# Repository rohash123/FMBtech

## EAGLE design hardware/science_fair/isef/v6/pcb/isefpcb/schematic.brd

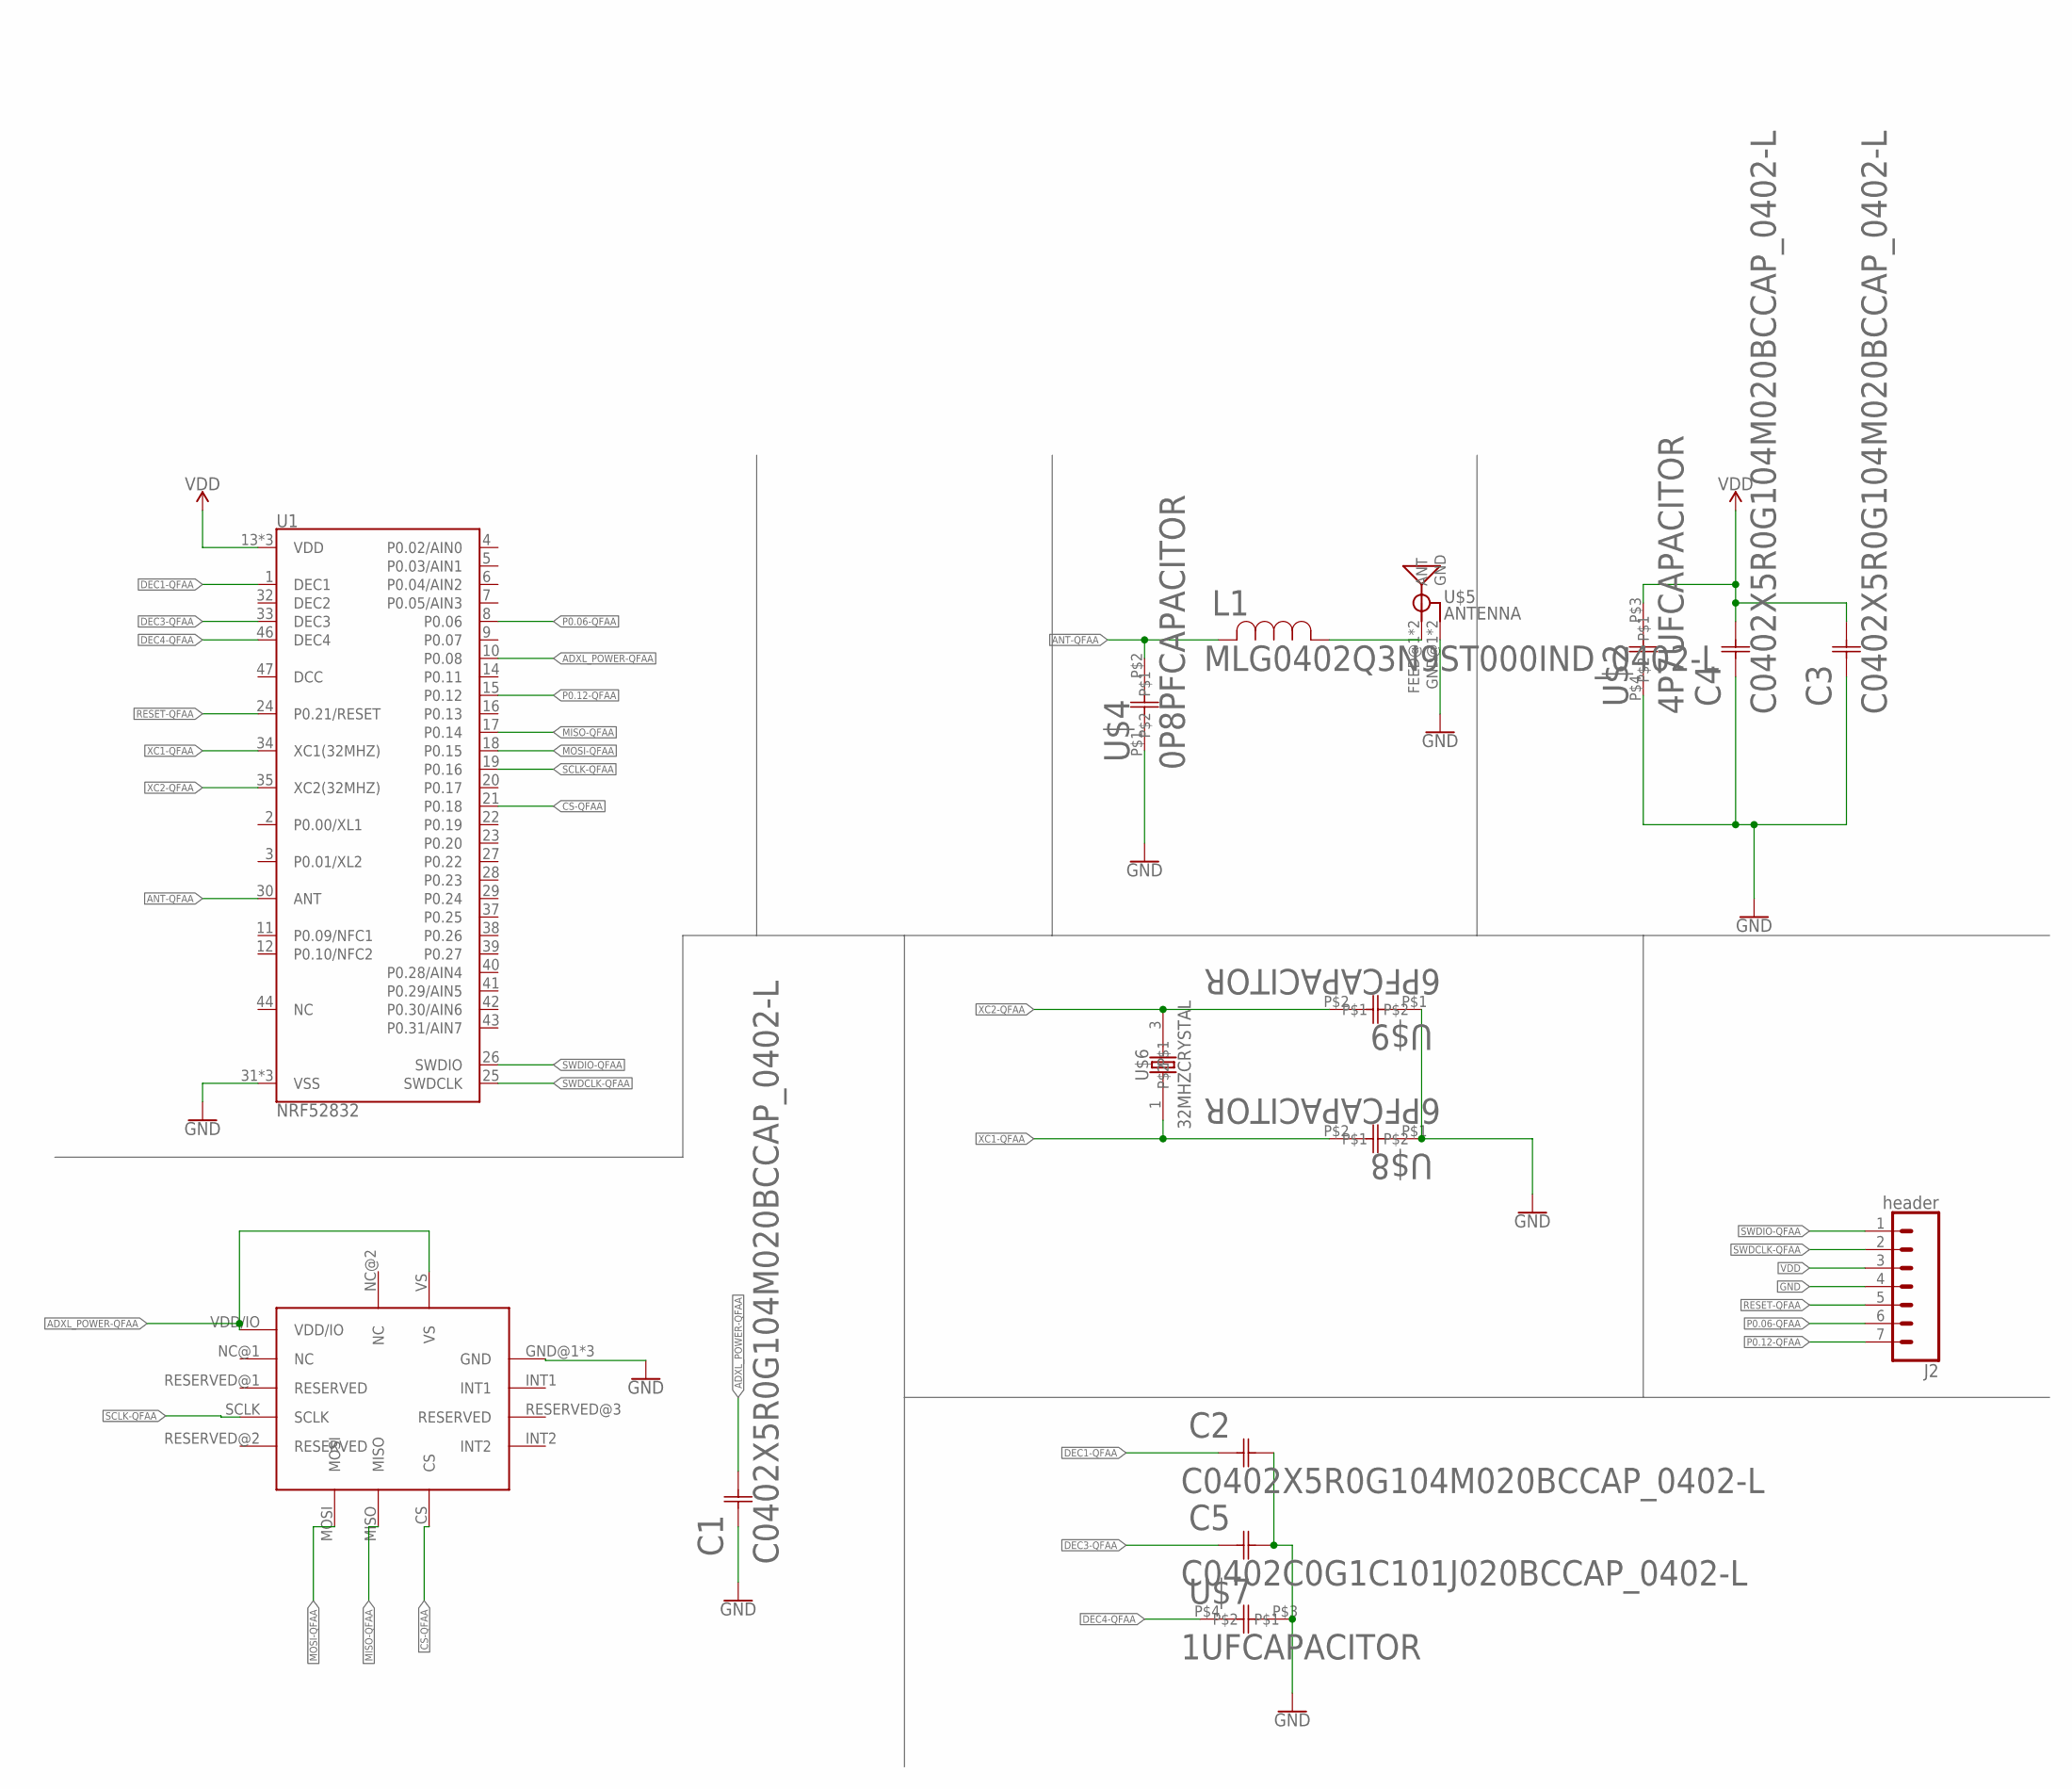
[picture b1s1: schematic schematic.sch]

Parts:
C1, C2, C3, C4: C0402X5R0G104M020BCCAP_0402-L; CAP_0402-L
C5: C0402C0G1C101J020BCCAP_0402-L; CAP_0402-L
J2: header; 1X07
L1: MLG0402Q3N9ST000IND_0402-L; IND_0402-L
U1: NRF52832; QFN48-6X6MM
U$1: ADXL362; TFLGA-16/3.3MMX3.1MM
U$2: 4P7UFCAPACITOR
U$4: 0P8PFCAPACITOR
U$5: ANTENNA; ANTENNA_FOOTPRINT
U$6: 32MHZCRYSTAL
U$7: 1UFCAPACITOR
U$8, U$9: 6PFCAPACITOR

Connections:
ADXL_POWER-QFAA: C1.2 (22), U1.10 (P0.08), U$1.VDD/IO, U$1.VS
ANT-QFAA: L1.2, U1.30 (ANT), U$4.P$2
CS-QFAA: U1.21 (P0.18), U$1.CS
DEC1-QFAA: C2.1 (11), U1.1 (DEC1)
DEC3-QFAA: C5.1 (11), U1.33 (DEC3)
DEC4-QFAA: U1.46 (DEC4), U$7.P$4
GND: C1.1 (11), C2.2 (22), C3.1 (11), C4.1 (11), C5.2 (22), J2.4, U1.31 (VSS), U1.45 (VSS), U1.EP (VSS), U$1.GND@1 (GND), U$1.GND@2 (GND), U$1.GND@3 (GND), U$2.P$4, U$4.P$1, U$5.GND@1 (GND), U$5.GND@2 (GND), U$7.P$3, U$8.P$1, U$9.P$1
MISO-QFAA: U1.17 (P0.14), U$1.MISO
MOSI-QFAA: U1.18 (P0.15), U$1.MOSI
unnamed: L1.1, U$5.FEED@1 (ANT), U$5.FEED@2 (ANT)
P0.06-QFAA: J2.6, U1.8 (P0.06)
P0.12-QFAA: J2.7, U1.15 (P0.12)
RESET-QFAA: J2.5, U1.24 (P0.21/RESET)
SCLK-QFAA: U1.19 (P0.16), U$1.SCLK
SWDCLK-QFAA: J2.2, U1.25 (SWDCLK)
SWDIO-QFAA: J2.1, U1.26 (SWDIO)
VDD: C3.2 (22), C4.2 (22), J2.3, U1.13 (VDD), U1.36 (VDD), U1.48 (VDD), U$2.P$3
XC1-QFAA: U1.34 (XC1(32MHZ)), U$6.1, U$8.P$2
XC2-QFAA: U1.35 (XC2(32MHZ)), U$6.3, U$9.P$2

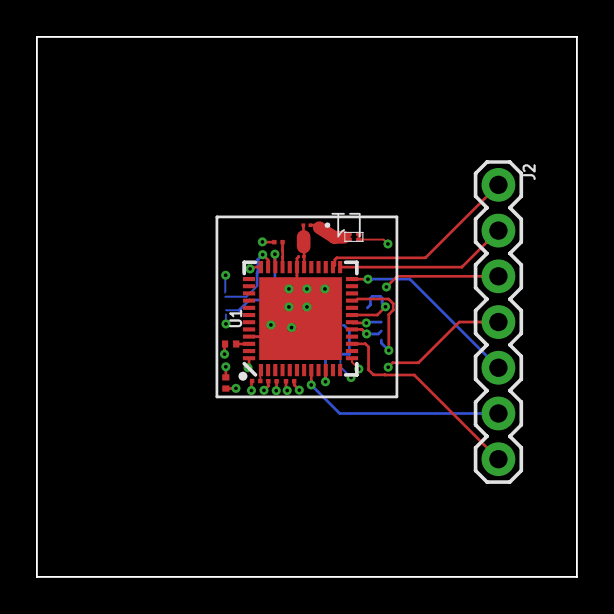
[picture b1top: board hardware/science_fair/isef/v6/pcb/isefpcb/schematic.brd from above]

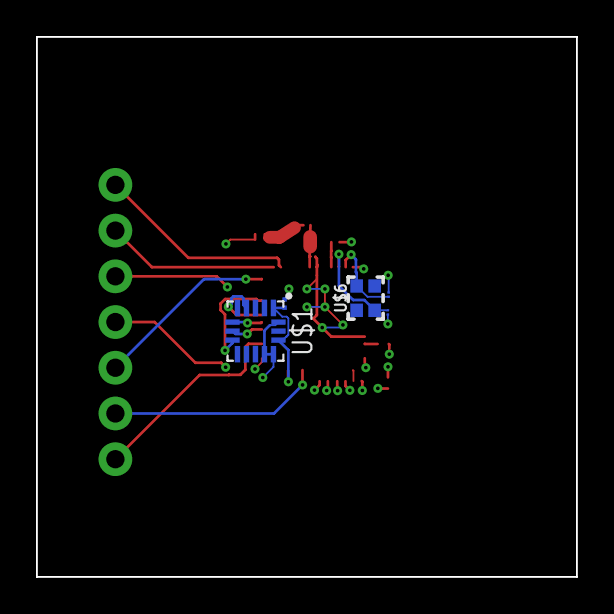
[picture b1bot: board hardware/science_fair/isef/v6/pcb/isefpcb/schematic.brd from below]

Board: 6 copper layers, 30.0 x 30.0 mm, 16 parts (5 on the bottom side), 19 nets.

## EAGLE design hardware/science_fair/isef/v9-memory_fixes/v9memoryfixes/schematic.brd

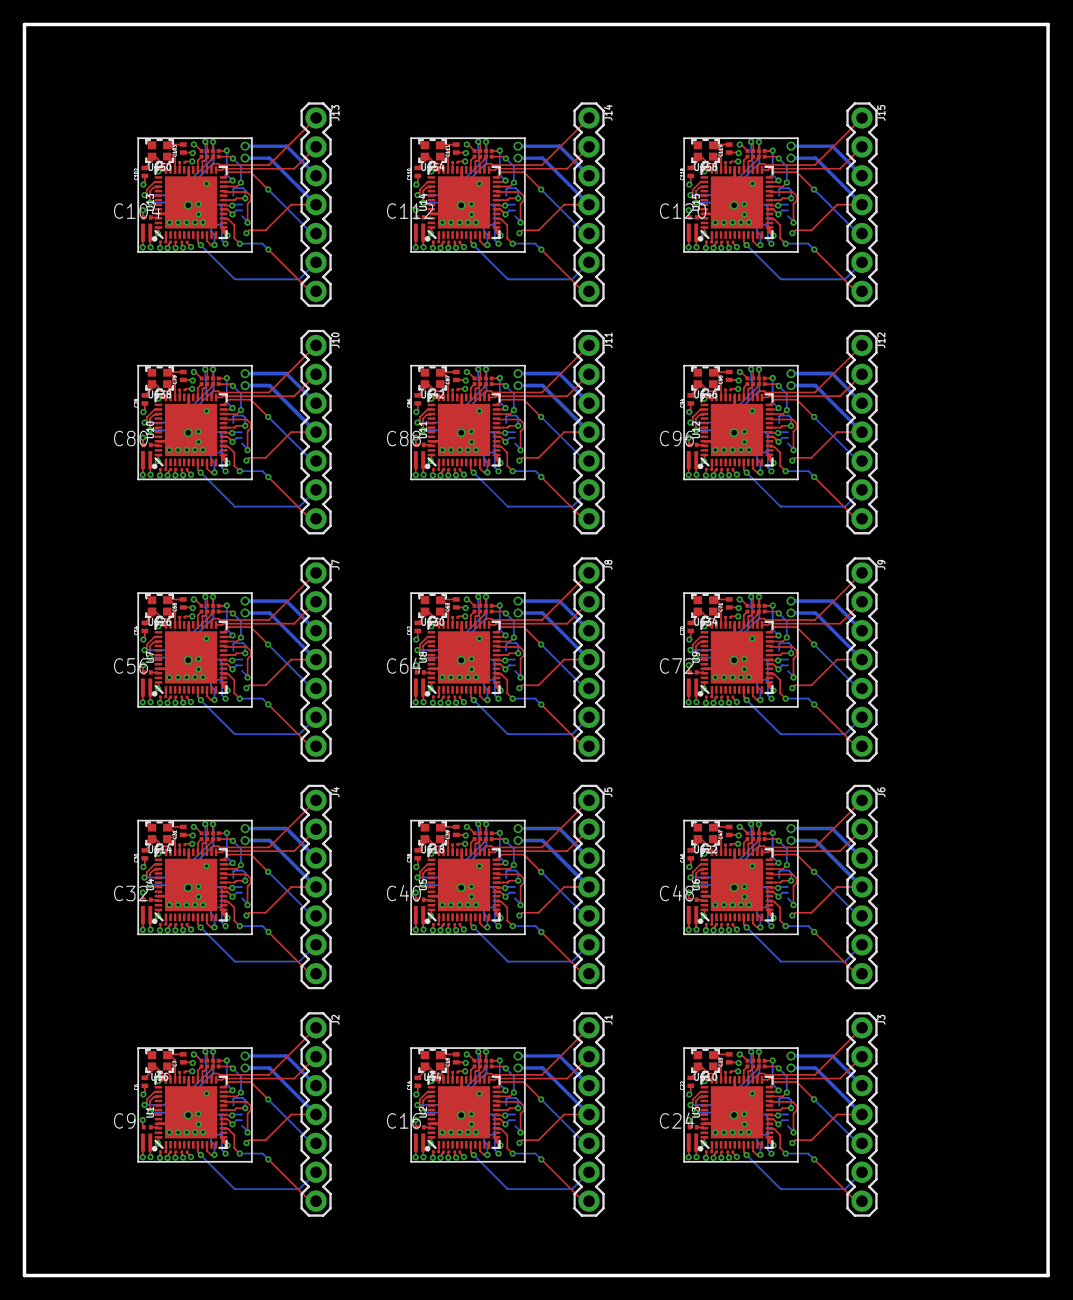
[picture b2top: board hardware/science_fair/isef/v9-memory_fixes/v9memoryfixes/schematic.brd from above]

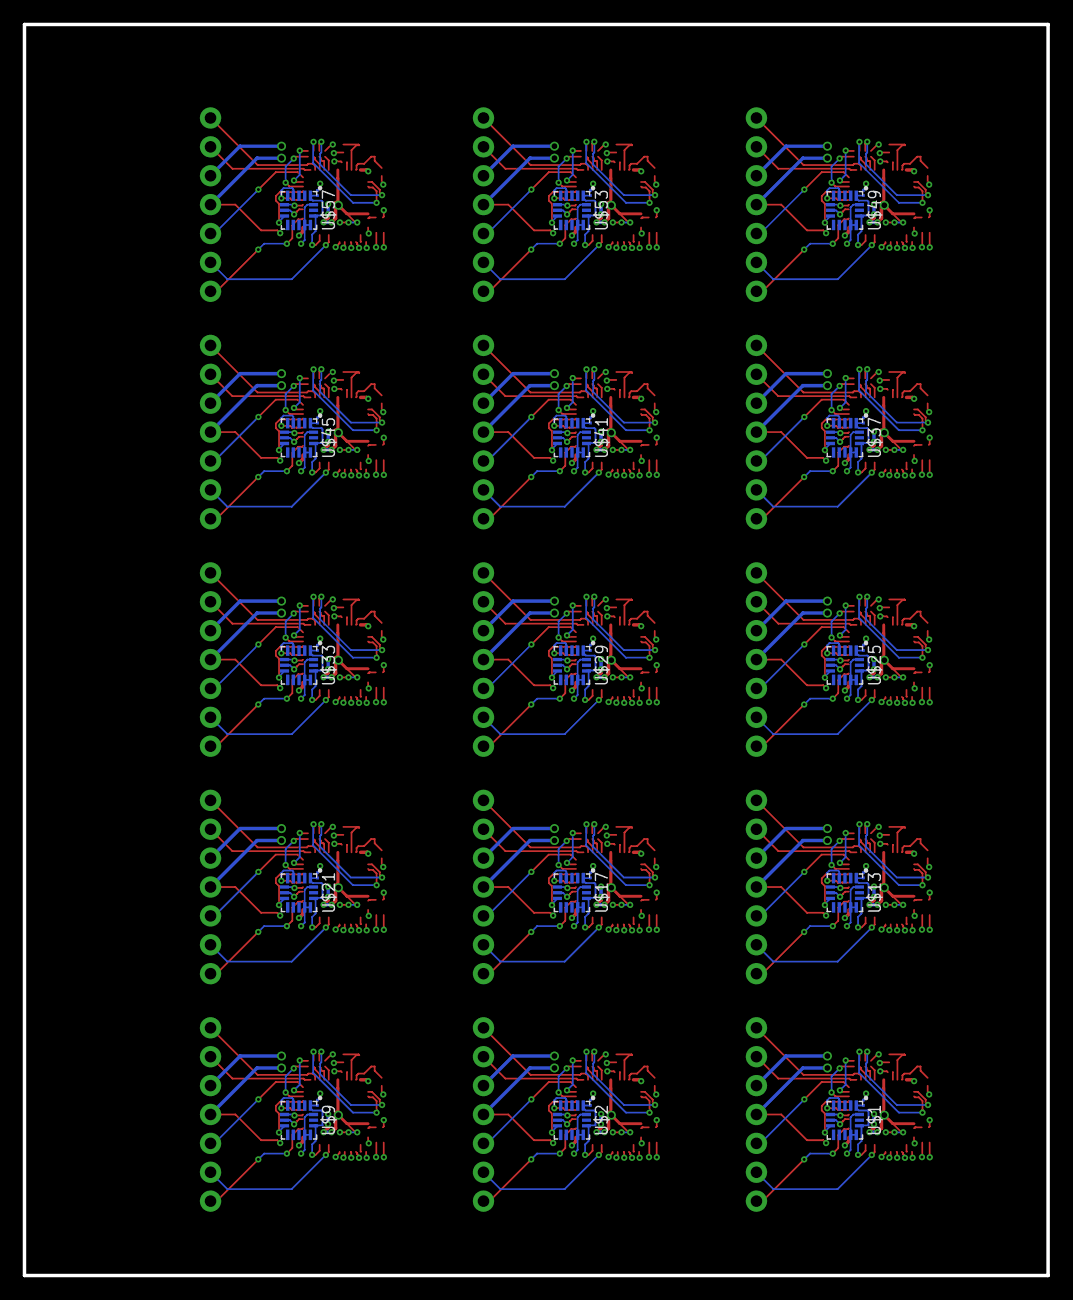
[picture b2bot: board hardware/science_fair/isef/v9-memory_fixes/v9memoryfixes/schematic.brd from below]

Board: 4 copper layers, 90.0 x 110.0 mm, 210 parts (30 on the bottom side), 360 nets.

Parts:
C1, C2, C3, C4, C8, C10, C11, C12, C17, C18, C19, C20, C25, C26, C27, C28, C33, C34, C35, C36, C41, C42, C43, C44, C49, C50, C51, C52, C57, C58, C59, C60, C65, C66, C67, C68, C73, C74, C75, C76, C81, C82, C83, C84, C89, C90, C91, C92, C97, C98, C99, C100, C105, C106, C107, C108, C113, C114, C115, C116: C0402X5R0G104M020BCCAP_0402-L; CAP_0402-L
C5, C13, C21, C29, C37, C45, C53, C61, C69, C77, C85, C93, C101, C109, C117: C0402C0G1C101J020BCCAP_0402-L; CAP_0402-L
C6, C7, C14, C15, C22, C23, C30, C31, C38, C39, C46, C47, C54, C55, C62, C63, C70, C71, C78, C79, C86, C87, C94, C95, C102, C103, C110, C111, C118, C119: GRM1555C1H6R0CA01D; CAPC1005X55N
C9, C16, C24, C32, C40, C48, C56, C64, C72, C80, C88, C96, C104, C112, C120: 4P7UFCAPACITOR4P7UFCAPACITOR; 4P7UFCAPACITOR
J1, J2, J3, J4, J5, J6, J7, J8, J9, J10, J11, J12, J13, J14, J15: header; 1X07
U1, U2, U3, U4, U5, U6, U7, U8, U9, U10, U11, U12, U13, U14, U15: NRF52832; QFN48-6X6MM
U$1, U$2, U$9, U$13, U$17, U$21, U$25, U$29, U$33, U$37, U$41, U$45, U$49, U$53, U$57: ADXL362; TFLGA-16/3.3MMX3.1MM
U$3, U$8, U$12, U$16, U$20, U$24, U$28, U$32, U$36, U$40, U$44, U$48, U$52, U$56, U$60: AT25SF161-UUD-T
U$4, U$6, U$10, U$14, U$18, U$22, U$26, U$30, U$34, U$38, U$42, U$46, U$50, U$54, U$58: 32MHZCRYSTAL
U$5, U$7, U$11, U$15, U$19, U$23, U$27, U$31, U$35, U$39, U$43, U$47, U$51, U$55, U$59: 1UFCAPACITOR

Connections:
ADXL_POWER-QFAA: C1.2, U1.10, U$1.VDD/IO, U$1.VS
ADXL_POWER-QFAA1: C8.2, U2.10, U$2.VDD/IO, U$2.VS
ADXL_POWER-QFAA2: C17.2, U3.10, U$9.VDD/IO, U$9.VS
ADXL_POWER-QFAA3: C25.2, U4.10, U$13.VDD/IO, U$13.VS
ADXL_POWER-QFAA4: C33.2, U5.10, U$17.VDD/IO, U$17.VS
ADXL_POWER-QFAA5: C41.2, U6.10, U$21.VDD/IO, U$21.VS
ADXL_POWER-QFAA6: C49.2, U7.10, U$25.VDD/IO, U$25.VS
ADXL_POWER-QFAA7: C57.2, U8.10, U$29.VDD/IO, U$29.VS
ADXL_POWER-QFAA8: C65.2, U9.10, U$33.VDD/IO, U$33.VS
ADXL_POWER-QFAA9: C73.2, U10.10, U$37.VDD/IO, U$37.VS
ADXL_POWER-QFAA10: C81.2, U11.10, U$41.VDD/IO, U$41.VS
ADXL_POWER-QFAA11: C89.2, U12.10, U$45.VDD/IO, U$45.VS
ADXL_POWER-QFAA12: C97.2, U13.10, U$49.VDD/IO, U$49.VS
ADXL_POWER-QFAA13: C105.2, U14.10, U$53.VDD/IO, U$53.VS
ADXL_POWER-QFAA14: C113.2, U15.10, U$57.VDD/IO, U$57.VS
CS-QFAA: U1.21, U$1.CS
CS-QFAA1: U2.21, U$2.CS
CS-QFAA2: U3.21, U$9.CS
CS-QFAA3: U4.21, U$13.CS
CS-QFAA4: U5.21, U$17.CS
CS-QFAA5: U6.21, U$21.CS
CS-QFAA6: U7.21, U$25.CS
CS-QFAA7: U8.21, U$29.CS
CS-QFAA8: U9.21, U$33.CS
CS-QFAA9: U10.21, U$37.CS
CS-QFAA10: U11.21, U$41.CS
CS-QFAA11: U12.21, U$45.CS
CS-QFAA12: U13.21, U$49.CS
CS-QFAA13: U14.21, U$53.CS
CS-QFAA14: U15.21, U$57.CS
CS_FLASH: U1.23, U$3.5
CS_FLASH1: U2.23, U$8.5
CS_FLASH2: U3.23, U$12.5
CS_FLASH3: U4.23, U$16.5
CS_FLASH4: U5.23, U$20.5
CS_FLASH5: U6.23, U$24.5
CS_FLASH6: U7.23, U$28.5
CS_FLASH7: U8.23, U$32.5
CS_FLASH8: U9.23, U$36.5
CS_FLASH9: U10.23, U$40.5
CS_FLASH10: U11.23, U$44.5
CS_FLASH11: U12.23, U$48.5
CS_FLASH12: U13.23, U$52.5
CS_FLASH13: U14.23, U$56.5
CS_FLASH14: U15.23, U$60.5
DEC1-QFAA: C2.1, U1.1
DEC1-QFAA1: C10.1, U2.1
DEC1-QFAA2: C18.1, U3.1
DEC1-QFAA3: C26.1, U4.1
DEC1-QFAA4: C34.1, U5.1
DEC1-QFAA5: C42.1, U6.1
DEC1-QFAA6: C50.1, U7.1
DEC1-QFAA7: C58.1, U8.1
DEC1-QFAA8: C66.1, U9.1
DEC1-QFAA9: C74.1, U10.1
DEC1-QFAA10: C82.1, U11.1
DEC1-QFAA11: C90.1, U12.1
DEC1-QFAA12: C98.1, U13.1
DEC1-QFAA13: C106.1, U14.1
DEC1-QFAA14: C114.1, U15.1
DEC3-QFAA: C5.1, U1.33
DEC3-QFAA1: C13.1, U2.33
DEC3-QFAA2: C21.1, U3.33
DEC3-QFAA3: C29.1, U4.33
DEC3-QFAA4: C37.1, U5.33
DEC3-QFAA5: C45.1, U6.33
DEC3-QFAA6: C53.1, U7.33
DEC3-QFAA7: C61.1, U8.33
DEC3-QFAA8: C69.1, U9.33
DEC3-QFAA9: C77.1, U10.33
DEC3-QFAA10: C85.1, U11.33
DEC3-QFAA11: C93.1, U12.33
DEC3-QFAA12: C101.1, U13.33
DEC3-QFAA13: C109.1, U14.33
DEC3-QFAA14: C117.1, U15.33
DEC4-QFAA: U1.46, U$7.P$4
DEC4-QFAA1: U2.46, U$5.P$4
DEC4-QFAA2: U3.46, U$11.P$4
DEC4-QFAA3: U4.46, U$15.P$4
DEC4-QFAA4: U5.46, U$19.P$4
DEC4-QFAA5: U6.46, U$23.P$4
DEC4-QFAA6: U7.46, U$27.P$4
DEC4-QFAA7: U8.46, U$31.P$4
DEC4-QFAA8: U9.46, U$35.P$4
DEC4-QFAA9: U10.46, U$39.P$4
DEC4-QFAA10: U11.46, U$43.P$4
DEC4-QFAA11: U12.46, U$47.P$4
DEC4-QFAA12: U13.46, U$51.P$4
DEC4-QFAA13: U14.46, U$55.P$4
DEC4-QFAA14: U15.46, U$59.P$4
FLASH_POWER: U1.22, U$3.1
FLASH_POWER1: U2.22, U$8.1
FLASH_POWER2: U3.22, U$12.1
FLASH_POWER3: U4.22, U$16.1
FLASH_POWER4: U5.22, U$20.1
FLASH_POWER5: U6.22, U$24.1
FLASH_POWER6: U7.22, U$28.1
FLASH_POWER7: U8.22, U$32.1
FLASH_POWER8: U9.22, U$36.1
FLASH_POWER9: U10.22, U$40.1
FLASH_POWER10: U11.22, U$44.1
FLASH_POWER11: U12.22, U$48.1
FLASH_POWER12: U13.22, U$52.1
FLASH_POWER13: U14.22, U$56.1
FLASH_POWER14: U15.22, U$60.1
GND: C1.1, C2.2, C3.1, C4.1, C5.2, C6.1, C7.1, C9.1, J2.4, U1.31, U1.45, U1.EP, U$1.GND@1, U$1.GND@2, U$1.GND@3, U$3.8, U$7.P$3
GND1: C8.1, C10.2, C11.1, C12.1, C13.2, C14.1, C15.1, C16.1, J1.4, U2.31, U2.45, U2.EP, U$2.GND@1, U$2.GND@2, U$2.GND@3, U$5.P$3, U$8.8
GND2: C17.1, C18.2, C19.1, C20.1, C21.2, C22.1, C23.1, C24.1, J3.4, U3.31, U3.45, U3.EP, U$9.GND@1, U$9.GND@2, U$9.GND@3, U$11.P$3, U$12.8
GND3: C25.1, C26.2, C27.1, C28.1, C29.2, C30.1, C31.1, C32.1, J4.4, U4.31, U4.45, U4.EP, U$13.GND@1, U$13.GND@2, U$13.GND@3, U$15.P$3, U$16.8
GND4: C33.1, C34.2, C35.1, C36.1, C37.2, C38.1, C39.1, C40.1, J5.4, U5.31, U5.45, U5.EP, U$17.GND@1, U$17.GND@2, U$17.GND@3, U$19.P$3, U$20.8
GND5: C41.1, C42.2, C43.1, C44.1, C45.2, C46.1, C47.1, C48.1, J6.4, U6.31, U6.45, U6.EP, U$21.GND@1, U$21.GND@2, U$21.GND@3, U$23.P$3, U$24.8
GND6: C49.1, C50.2, C51.1, C52.1, C53.2, C54.1, C55.1, C56.1, J7.4, U7.31, U7.45, U7.EP, U$25.GND@1, U$25.GND@2, U$25.GND@3, U$27.P$3, U$28.8
GND7: C57.1, C58.2, C59.1, C60.1, C61.2, C62.1, C63.1, C64.1, J8.4, U8.31, U8.45, U8.EP, U$29.GND@1, U$29.GND@2, U$29.GND@3, U$31.P$3, U$32.8
GND8: C65.1, C66.2, C67.1, C68.1, C69.2, C70.1, C71.1, C72.1, J9.4, U9.31, U9.45, U9.EP, U$33.GND@1, U$33.GND@2, U$33.GND@3, U$35.P$3, U$36.8
GND9: C73.1, C74.2, C75.1, C76.1, C77.2, C78.1, C79.1, C80.1, J10.4, U10.31, U10.45, U10.EP, U$37.GND@1, U$37.GND@2, U$37.GND@3, U$39.P$3, U$40.8
GND10: C81.1, C82.2, C83.1, C84.1, C85.2, C86.1, C87.1, C88.1, J11.4, U11.31, U11.45, U11.EP, U$41.GND@1, U$41.GND@2, U$41.GND@3, U$43.P$3, U$44.8
GND11: C89.1, C90.2, C91.1, C92.1, C93.2, C94.1, C95.1, C96.1, J12.4, U12.31, U12.45, U12.EP, U$45.GND@1, U$45.GND@2, U$45.GND@3, U$47.P$3, U$48.8
GND12: C97.1, C98.2, C99.1, C100.1, C101.2, C102.1, C103.1, C104.1, J13.4, U13.31, U13.45, U13.EP, U$49.GND@1, U$49.GND@2, U$49.GND@3, U$51.P$3, U$52.8
GND13: C105.1, C106.2, C107.1, C108.1, C109.2, C110.1, C111.1, C112.1, J14.4, U14.31, U14.45, U14.EP, U$53.GND@1, U$53.GND@2, U$53.GND@3, U$55.P$3, U$56.8
GND14: C113.1, C114.2, C115.1, C116.1, C117.2, C118.1, C119.1, C120.1, J15.4, U15.31, U15.45, U15.EP, U$57.GND@1, U$57.GND@2, U$57.GND@3, U$59.P$3, U$60.8
HOLD_FLASH: U1.27, U$3.2
HOLD_FLASH1: U2.27, U$8.2
HOLD_FLASH2: U3.27, U$12.2
HOLD_FLASH3: U4.27, U$16.2
HOLD_FLASH4: U5.27, U$20.2
HOLD_FLASH5: U6.27, U$24.2
HOLD_FLASH6: U7.27, U$28.2
HOLD_FLASH7: U8.27, U$32.2
HOLD_FLASH8: U9.27, U$36.2
HOLD_FLASH9: U10.27, U$40.2
HOLD_FLASH10: U11.27, U$44.2
HOLD_FLASH11: U12.27, U$48.2
HOLD_FLASH12: U13.27, U$52.2
HOLD_FLASH13: U14.27, U$56.2
HOLD_FLASH14: U15.27, U$60.2
MISO-QFAA: U1.17, U$1.MISO
MISO-QFAA1: U2.17, U$2.MISO
MISO-QFAA2: U3.17, U$9.MISO
MISO-QFAA3: U4.17, U$13.MISO
MISO-QFAA4: U5.17, U$17.MISO
MISO-QFAA5: U6.17, U$21.MISO
MISO-QFAA6: U7.17, U$25.MISO
MISO-QFAA7: U8.17, U$29.MISO
MISO-QFAA8: U9.17, U$33.MISO
MISO-QFAA9: U10.17, U$37.MISO
MISO-QFAA10: U11.17, U$41.MISO
MISO-QFAA11: U12.17, U$45.MISO
MISO-QFAA12: U13.17, U$49.MISO
MISO-QFAA13: U14.17, U$53.MISO
MISO-QFAA14: U15.17, U$57.MISO
MOSI-QFAA: U1.18, U$1.MOSI
MOSI-QFAA1: U2.18, U$2.MOSI
MOSI-QFAA2: U3.18, U$9.MOSI
MOSI-QFAA3: U4.18, U$13.MOSI
MOSI-QFAA4: U5.18, U$17.MOSI
MOSI-QFAA5: U6.18, U$21.MOSI
MOSI-QFAA6: U7.18, U$25.MOSI
MOSI-QFAA7: U8.18, U$29.MOSI
MOSI-QFAA8: U9.18, U$33.MOSI
MOSI-QFAA9: U10.18, U$37.MOSI
MOSI-QFAA10: U11.18, U$41.MOSI
MOSI-QFAA11: U12.18, U$45.MOSI
MOSI-QFAA12: U13.18, U$49.MOSI
MOSI-QFAA13: U14.18, U$53.MOSI
MOSI-QFAA14: U15.18, U$57.MOSI
P0.06-QFAA: J2.6, U1.8
P0.06-QFAA1: J1.6, U2.8
P0.06-QFAA2: J3.6, U3.8
P0.06-QFAA3: J4.6, U4.8
P0.06-QFAA4: J5.6, U5.8
P0.06-QFAA5: J6.6, U6.8
P0.06-QFAA6: J7.6, U7.8
P0.06-QFAA7: J8.6, U8.8
P0.06-QFAA8: J9.6, U9.8
P0.06-QFAA9: J10.6, U10.8
P0.06-QFAA10: J11.6, U11.8
P0.06-QFAA11: J12.6, U12.8
P0.06-QFAA12: J13.6, U13.8
P0.06-QFAA13: J14.6, U14.8
P0.06-QFAA14: J15.6, U15.8
P0.12-QFAA: J2.7, U1.15
P0.12-QFAA1: J1.7, U2.15
P0.12-QFAA2: J3.7, U3.15
P0.12-QFAA3: J4.7, U4.15
P0.12-QFAA4: J5.7, U5.15
P0.12-QFAA5: J6.7, U6.15
P0.12-QFAA6: J7.7, U7.15
P0.12-QFAA7: J8.7, U8.15
P0.12-QFAA8: J9.7, U9.15
P0.12-QFAA9: J10.7, U10.15
P0.12-QFAA10: J11.7, U11.15
P0.12-QFAA11: J12.7, U12.15
P0.12-QFAA12: J13.7, U13.15
P0.12-QFAA13: J14.7, U14.15
P0.12-QFAA14: J15.7, U15.15
RESET-QFAA: J2.5, U1.24
RESET-QFAA1: J1.5, U2.24
RESET-QFAA2: J3.5, U3.24
RESET-QFAA3: J4.5, U4.24
RESET-QFAA4: J5.5, U5.24
RESET-QFAA5: J6.5, U6.24
RESET-QFAA6: J7.5, U7.24
RESET-QFAA7: J8.5, U8.24
RESET-QFAA8: J9.5, U9.24
RESET-QFAA9: J10.5, U10.24
RESET-QFAA10: J11.5, U11.24
RESET-QFAA11: J12.5, U12.24
RESET-QFAA12: J13.5, U13.24
RESET-QFAA13: J14.5, U14.24
RESET-QFAA14: J15.5, U15.24
SCK_FLASH: U1.28, U$3.3
SCK_FLASH1: U2.28, U$8.3
SCK_FLASH2: U3.28, U$12.3
SCK_FLASH3: U4.28, U$16.3
SCK_FLASH4: U5.28, U$20.3
SCK_FLASH5: U6.28, U$24.3
SCK_FLASH6: U7.28, U$28.3
SCK_FLASH7: U8.28, U$32.3
SCK_FLASH8: U9.28, U$36.3
SCK_FLASH9: U10.28, U$40.3
SCK_FLASH10: U11.28, U$44.3
SCK_FLASH11: U12.28, U$48.3
SCK_FLASH12: U13.28, U$52.3
SCK_FLASH13: U14.28, U$56.3
SCK_FLASH14: U15.28, U$60.3
SCLK-QFAA: U1.19, U$1.SCLK
SCLK-QFAA1: U2.19, U$2.SCLK
SCLK-QFAA2: U3.19, U$9.SCLK
SCLK-QFAA3: U4.19, U$13.SCLK
SCLK-QFAA4: U5.19, U$17.SCLK
SCLK-QFAA5: U6.19, U$21.SCLK
SCLK-QFAA6: U7.19, U$25.SCLK
SCLK-QFAA7: U8.19, U$29.SCLK
SCLK-QFAA8: U9.19, U$33.SCLK
SCLK-QFAA9: U10.19, U$37.SCLK
SCLK-QFAA10: U11.19, U$41.SCLK
SCLK-QFAA11: U12.19, U$45.SCLK
SCLK-QFAA12: U13.19, U$49.SCLK
SCLK-QFAA13: U14.19, U$53.SCLK
SCLK-QFAA14: U15.19, U$57.SCLK
SI_FLASH: U1.29, U$3.4
SI_FLASH1: U2.29, U$8.4
SI_FLASH2: U3.29, U$12.4
SI_FLASH3: U4.29, U$16.4
SI_FLASH4: U5.29, U$20.4
SI_FLASH5: U6.29, U$24.4
SI_FLASH6: U7.29, U$28.4
SI_FLASH7: U8.29, U$32.4
SI_FLASH8: U9.29, U$36.4
SI_FLASH9: U10.29, U$40.4
SI_FLASH10: U11.29, U$44.4
SI_FLASH11: U12.29, U$48.4
SI_FLASH12: U13.29, U$52.4
SI_FLASH13: U14.29, U$56.4
SI_FLASH14: U15.29, U$60.4
SO_FLASH: U1.39, U$3.6
SO_FLASH1: U2.39, U$8.6
SO_FLASH2: U3.39, U$12.6
SO_FLASH3: U4.39, U$16.6
SO_FLASH4: U5.39, U$20.6
SO_FLASH5: U6.39, U$24.6
SO_FLASH6: U7.39, U$28.6
SO_FLASH7: U8.39, U$32.6
SO_FLASH8: U9.39, U$36.6
SO_FLASH9: U10.39, U$40.6
SO_FLASH10: U11.39, U$44.6
SO_FLASH11: U12.39, U$48.6
SO_FLASH12: U13.39, U$52.6
SO_FLASH13: U14.39, U$56.6
SO_FLASH14: U15.39, U$60.6
SWDCLK-QFAA: J2.2, U1.25
SWDCLK-QFAA1: J1.2, U2.25
SWDCLK-QFAA2: J3.2, U3.25
SWDCLK-QFAA3: J4.2, U4.25
SWDCLK-QFAA4: J5.2, U5.25
SWDCLK-QFAA5: J6.2, U6.25
SWDCLK-QFAA6: J7.2, U7.25
SWDCLK-QFAA7: J8.2, U8.25
SWDCLK-QFAA8: J9.2, U9.25
SWDCLK-QFAA9: J10.2, U10.25
SWDCLK-QFAA10: J11.2, U11.25
SWDCLK-QFAA11: J12.2, U12.25
SWDCLK-QFAA12: J13.2, U13.25
SWDCLK-QFAA13: J14.2, U14.25
SWDCLK-QFAA14: J15.2, U15.25
SWDIO-QFAA: J2.1, U1.26
SWDIO-QFAA1: J1.1, U2.26
SWDIO-QFAA2: J3.1, U3.26
SWDIO-QFAA3: J4.1, U4.26
SWDIO-QFAA4: J5.1, U5.26
SWDIO-QFAA5: J6.1, U6.26
SWDIO-QFAA6: J7.1, U7.26
SWDIO-QFAA7: J8.1, U8.26
SWDIO-QFAA8: J9.1, U9.26
SWDIO-QFAA9: J10.1, U10.26
SWDIO-QFAA10: J11.1, U11.26
SWDIO-QFAA11: J12.1, U12.26
SWDIO-QFAA12: J13.1, U13.26
SWDIO-QFAA13: J14.1, U14.26
SWDIO-QFAA14: J15.1, U15.26
VDD: C3.2, C4.2, C9.2, J2.3, U1.13, U1.36, U1.48
VDD1: C11.2, C12.2, C16.2, J1.3, U2.13, U2.36, U2.48
VDD2: C19.2, C20.2, C24.2, J3.3, U3.13, U3.36, U3.48
VDD3: C27.2, C28.2, C32.2, J4.3, U4.13, U4.36, U4.48
VDD4: C35.2, C36.2, C40.2, J5.3, U5.13, U5.36, U5.48
VDD5: C43.2, C44.2, C48.2, J6.3, U6.13, U6.36, U6.48
VDD6: C51.2, C52.2, C56.2, J7.3, U7.13, U7.36, U7.48
VDD7: C59.2, C60.2, C64.2, J8.3, U8.13, U8.36, U8.48
VDD8: C67.2, C68.2, C72.2, J9.3, U9.13, U9.36, U9.48
VDD9: C75.2, C76.2, C80.2, J10.3, U10.13, U10.36, U10.48
VDD10: C83.2, C84.2, C88.2, J11.3, U11.13, U11.36, U11.48
VDD11: C91.2, C92.2, C96.2, J12.3, U12.13, U12.36, U12.48
VDD12: C99.2, C100.2, C104.2, J13.3, U13.13, U13.36, U13.48
VDD13: C107.2, C108.2, C112.2, J14.3, U14.13, U14.36, U14.48
VDD14: C115.2, C116.2, C120.2, J15.3, U15.13, U15.36, U15.48
WP_FLASH: U1.38, U$3.7
WP_FLASH1: U2.38, U$8.7
WP_FLASH2: U3.38, U$12.7
WP_FLASH3: U4.38, U$16.7
WP_FLASH4: U5.38, U$20.7
WP_FLASH5: U6.38, U$24.7
WP_FLASH6: U7.38, U$28.7
WP_FLASH7: U8.38, U$32.7
WP_FLASH8: U9.38, U$36.7
WP_FLASH9: U10.38, U$40.7
WP_FLASH10: U11.38, U$44.7
WP_FLASH11: U12.38, U$48.7
WP_FLASH12: U13.38, U$52.7
WP_FLASH13: U14.38, U$56.7
WP_FLASH14: U15.38, U$60.7
XC1-QFAA: C7.2, U1.34, U$6.1
XC1-QFAA1: C15.2, U2.34, U$4.1
XC1-QFAA2: C23.2, U3.34, U$10.1
XC1-QFAA3: C31.2, U4.34, U$14.1
XC1-QFAA4: C39.2, U5.34, U$18.1
XC1-QFAA5: C47.2, U6.34, U$22.1
XC1-QFAA6: C55.2, U7.34, U$26.1
XC1-QFAA7: C63.2, U8.34, U$30.1
XC1-QFAA8: C71.2, U9.34, U$34.1
XC1-QFAA9: C79.2, U10.34, U$38.1
XC1-QFAA10: C87.2, U11.34, U$42.1
XC1-QFAA11: C95.2, U12.34, U$46.1
XC1-QFAA12: C103.2, U13.34, U$50.1
XC1-QFAA13: C111.2, U14.34, U$54.1
XC1-QFAA14: C119.2, U15.34, U$58.1
XC2-QFAA: C6.2, U1.35, U$6.3
XC2-QFAA1: C14.2, U2.35, U$4.3
XC2-QFAA2: C22.2, U3.35, U$10.3
XC2-QFAA3: C30.2, U4.35, U$14.3
XC2-QFAA4: C38.2, U5.35, U$18.3
XC2-QFAA5: C46.2, U6.35, U$22.3
XC2-QFAA6: C54.2, U7.35, U$26.3
XC2-QFAA7: C62.2, U8.35, U$30.3
XC2-QFAA8: C70.2, U9.35, U$34.3
XC2-QFAA9: C78.2, U10.35, U$38.3
XC2-QFAA10: C86.2, U11.35, U$42.3
XC2-QFAA11: C94.2, U12.35, U$46.3
XC2-QFAA12: C102.2, U13.35, U$50.3
XC2-QFAA13: C110.2, U14.35, U$54.3
XC2-QFAA14: C118.2, U15.35, U$58.3

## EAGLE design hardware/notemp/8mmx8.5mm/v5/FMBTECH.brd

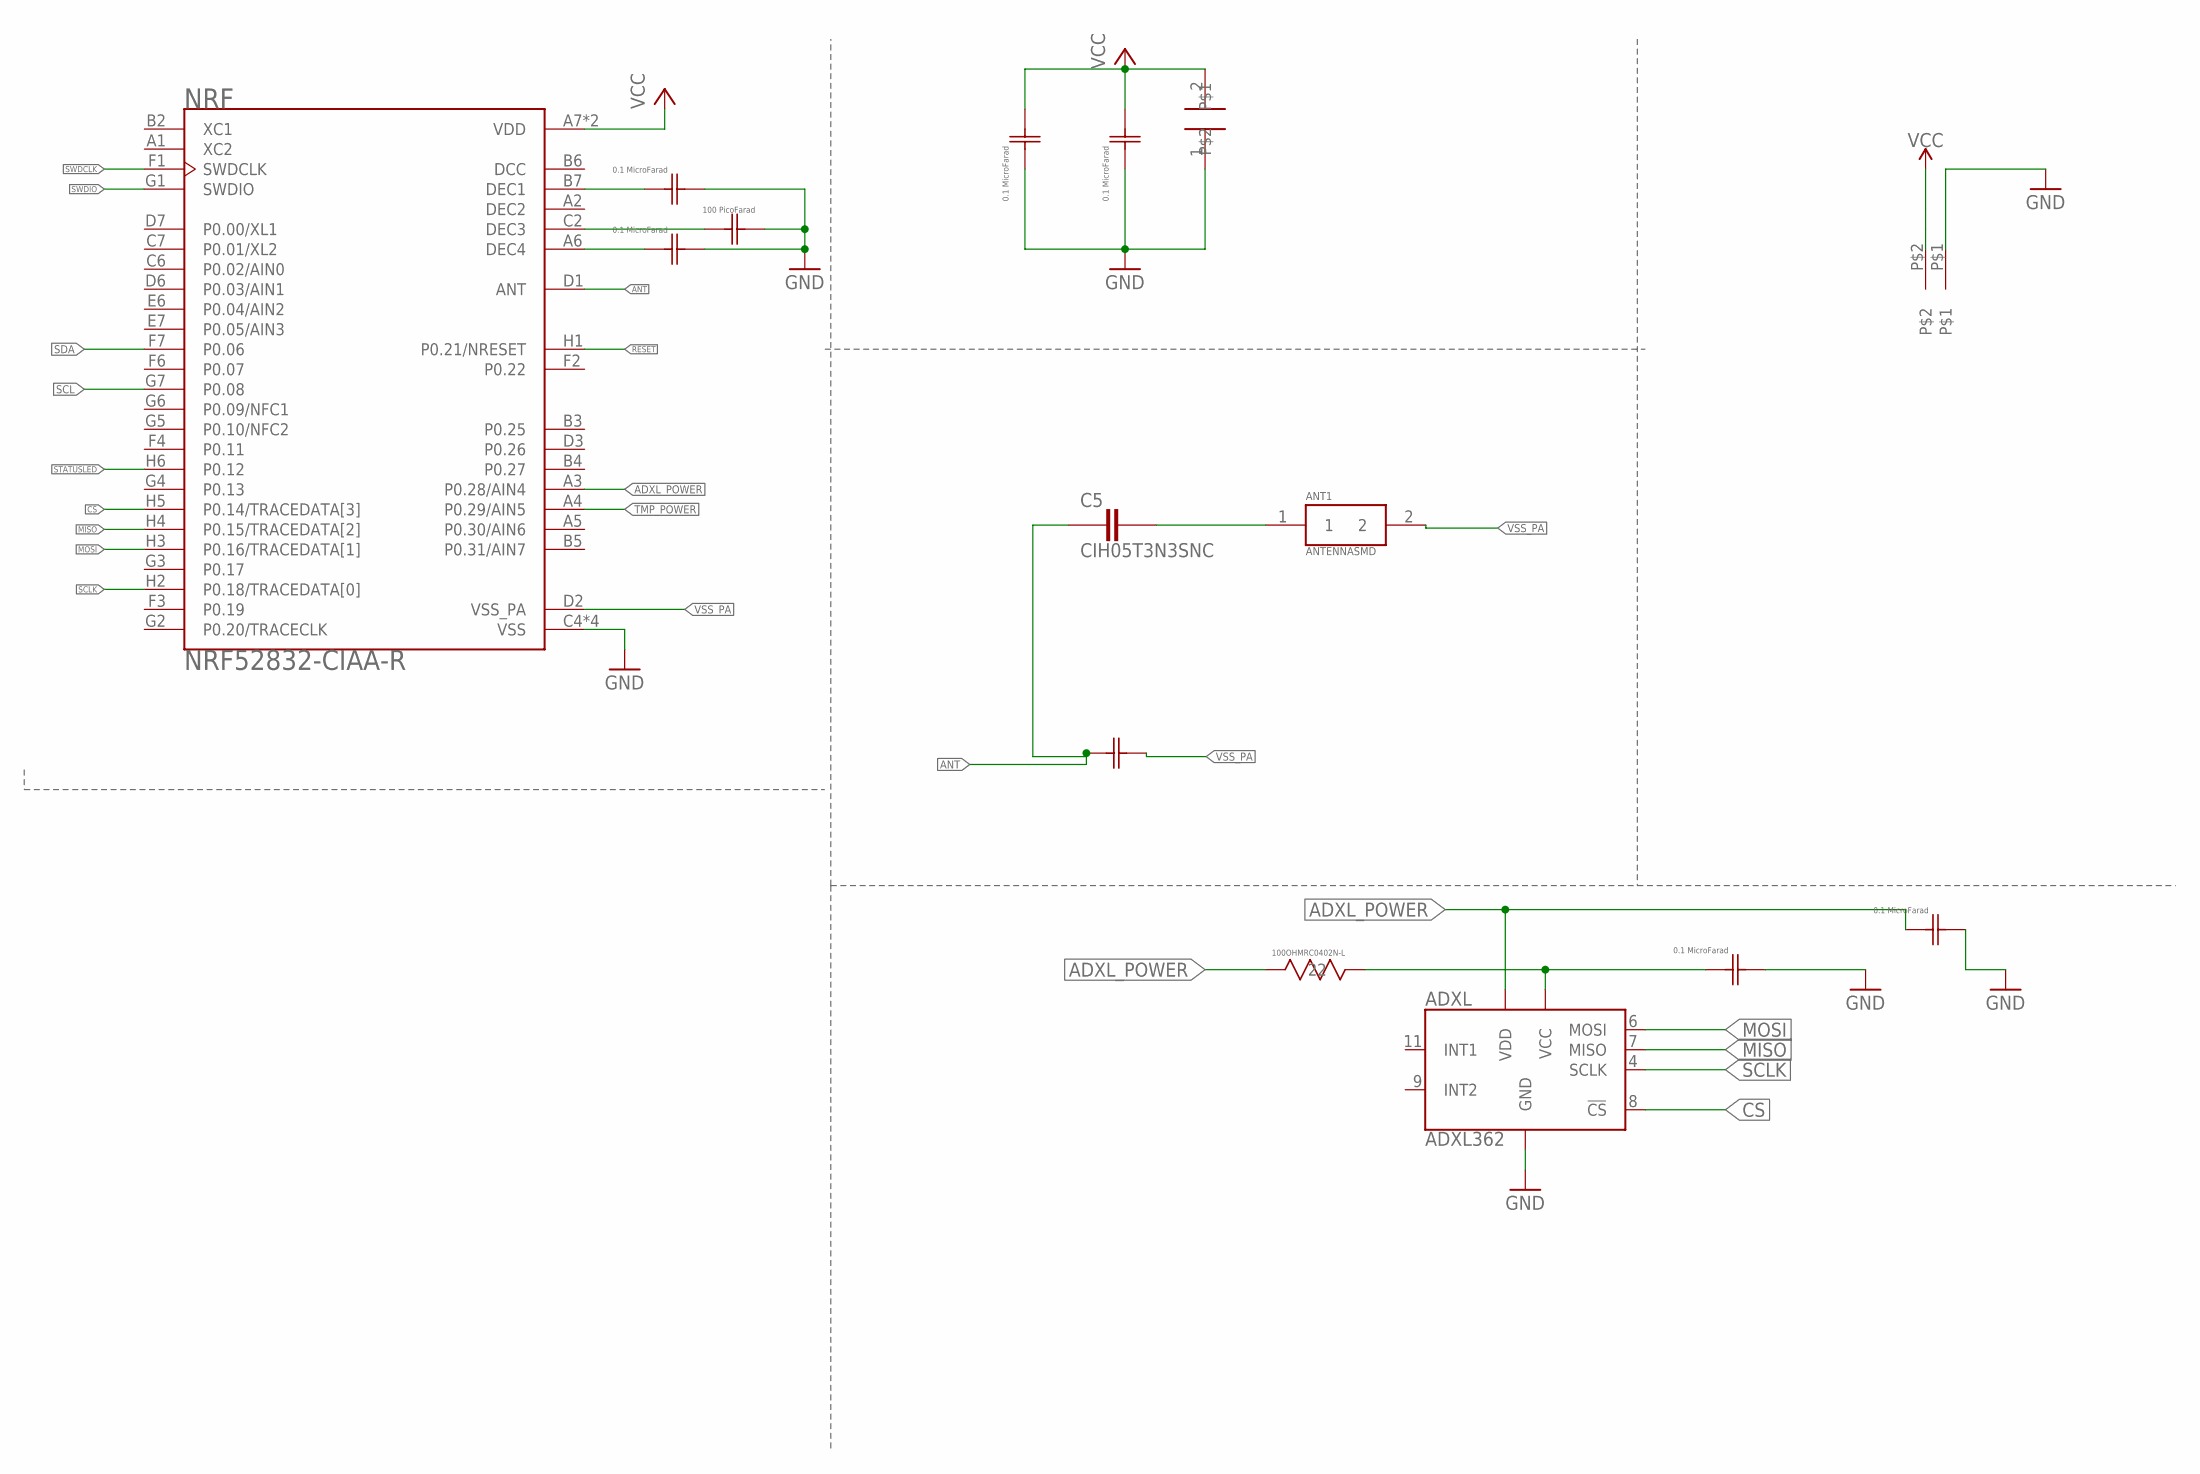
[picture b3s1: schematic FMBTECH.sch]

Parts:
ADXL: ADXL362; TFLGA-16/3.3MMX3.1MM
ANT1: ANTENNASMD; 1
C1, C2, C6, C7, C8, C9: 02016D104KAT2A; 0201
C3: GRM0335C1E101JA01D; G-033
C4: GJM1555C1H1R0BB01DG-155-L; G-155-L
C5: CIH05T3N3SNC; CAPC1005X55N
NRF: NRF52832-CIAA-R; BGA50N40P7X8_300X320X40
R6: 100OHMRC0402N-L; RES
U$1: 4.7µF; CAP
U$4: SUPPLY

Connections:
ADXL_POWER: ADXL.1 (VDD), C9.1, NRF.A3 (P0.28/AIN4), R6.1 (11)
ANT: C4.1 (11), C5.1, NRF.D1 (ANT)
CS: ADXL.8 (!CS), NRF.H5 (P0.14/TRACEDATA[3])
DCC: NRF.B6 (DCC)
DEC2: NRF.A2 (DEC2)
GND: ADXL.12 (GND), ADXL.13 (GND), ADXL.16 (GND), C1.2, C2.2, C3.2 (22), C6.1, C7.1, C8.2, C9.2, NRF.C4 (VSS), NRF.C5 (VSS), NRF.E3 (VSS), NRF.F5 (VSS), U$1.1, U$4.P$1
MISO: ADXL.7 (MISO), NRF.H4 (P0.15/TRACEDATA[2])
MOSI: ADXL.6 (MOSI), NRF.H3 (P0.16/TRACEDATA[1])
unnamed: ANT1.1, C5.2
unnamed: C2.1, NRF.A6 (DEC4)
unnamed: C1.1, NRF.B7 (DEC1)
unnamed: C3.1 (11), NRF.C2 (DEC3)
unnamed: ADXL.14 (VCC), C8.1, R6.2 (22)
RESET: NRF.H1 (P0.21/NRESET)
SCL: NRF.G7 (P0.08)
SCLK: ADXL.4 (SCLK), NRF.H2 (P0.18/TRACEDATA[0])
SDA: NRF.F7 (P0.06)
STATUSLED: NRF.H6 (P0.12)
SWDCLK: NRF.F1 (SWDCLK)
SWDIO: NRF.G1 (SWDIO)
TMP_POWER: NRF.A4 (P0.29/AIN5)
VCC: C6.2, C7.2, NRF.A7 (VDD), NRF.H7 (VDD), U$1.2, U$4.P$2
VSS_PA: ANT1.2, C4.2 (22), NRF.D2 (VSS_PA)

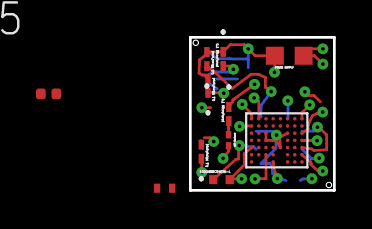
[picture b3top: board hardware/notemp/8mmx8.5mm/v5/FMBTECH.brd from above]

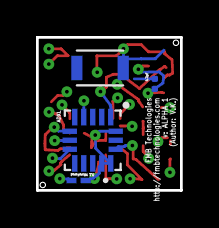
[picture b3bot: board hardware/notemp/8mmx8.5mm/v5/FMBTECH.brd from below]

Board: 6 copper layers, 8.0 x 8.5 mm, 15 parts (4 on the bottom side), 14 nets.

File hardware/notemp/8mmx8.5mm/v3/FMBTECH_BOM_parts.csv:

"Part";"Value";"Device";"Package";"Description";"";
"ADXL";"ADXL362";"ADXL362";"TFLGA-16/3.3MMX3.1MM";"IC ACCEL DIG LO PWR 3AX 16LGA";"";
"ANT1";"ANTENNASMD";"ANTENNASMD";"1";"";"";
"C1";"02016D104KAT2A";"02016D104KAT2A";"0201";"";"";
"C2";"02016D104KAT2A";"02016D104KAT2A";"0201";"";"";
"C3";"GRM0335C1E101JA01D";"GRM0335C1E101JA01D";"G-033";"";"";
"C6";"02016D104KAT2A";"02016D104KAT2A";"0201";"";"";
"C7";"02016D104KAT2A";"02016D104KAT2A";"0201";"";"";
"C8";"02016D104KAT2A";"02016D104KAT2A";"0201";"";"";
"C9";"02016D104KAT2A";"02016D104KAT2A";"0201";"";"";
"NRF";"NRF52832-CIAA-R";"NRF52832-CIAA-R";"BGA50N40P7X8_300X320X40";"Multi Protocal Bluetooth Smart ANT 2.4GHz RF SoC (WL-CSP)";"";
"R6";"100OHMRC0402N-L";"100OHMRC0402N-L";"RES";"";"";
"U$1";"4.7µF";"4.7µF";"CAP";"";"";
"U$2";"0.8PF";"0.8PF";"CAP";"";"";
"U$3";"INDUCTOR";"INDUCTOR";"1";"";"";
"U$4";"SUPPLY";"SUPPLY";"SUPPLY";"";"";

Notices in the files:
parts and their libraries:
SparkFun-Aesthetics: Licensing: Creative Commons ShareAlike 4.0 International - https://creativecommons.org/licenses/by-sa/4.0
